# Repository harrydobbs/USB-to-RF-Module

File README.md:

# USB-to-RF-Module
STM32L4-based RF-to-USB dongle using a low-power NRF24 2.4GHz transceiver. <br>
This repository features a custom 3D printed case, firmware and drivers aswell as schematics and PCB layout.

## KiCAD 3D Model

## Assembled Module

## 3D Printed Case

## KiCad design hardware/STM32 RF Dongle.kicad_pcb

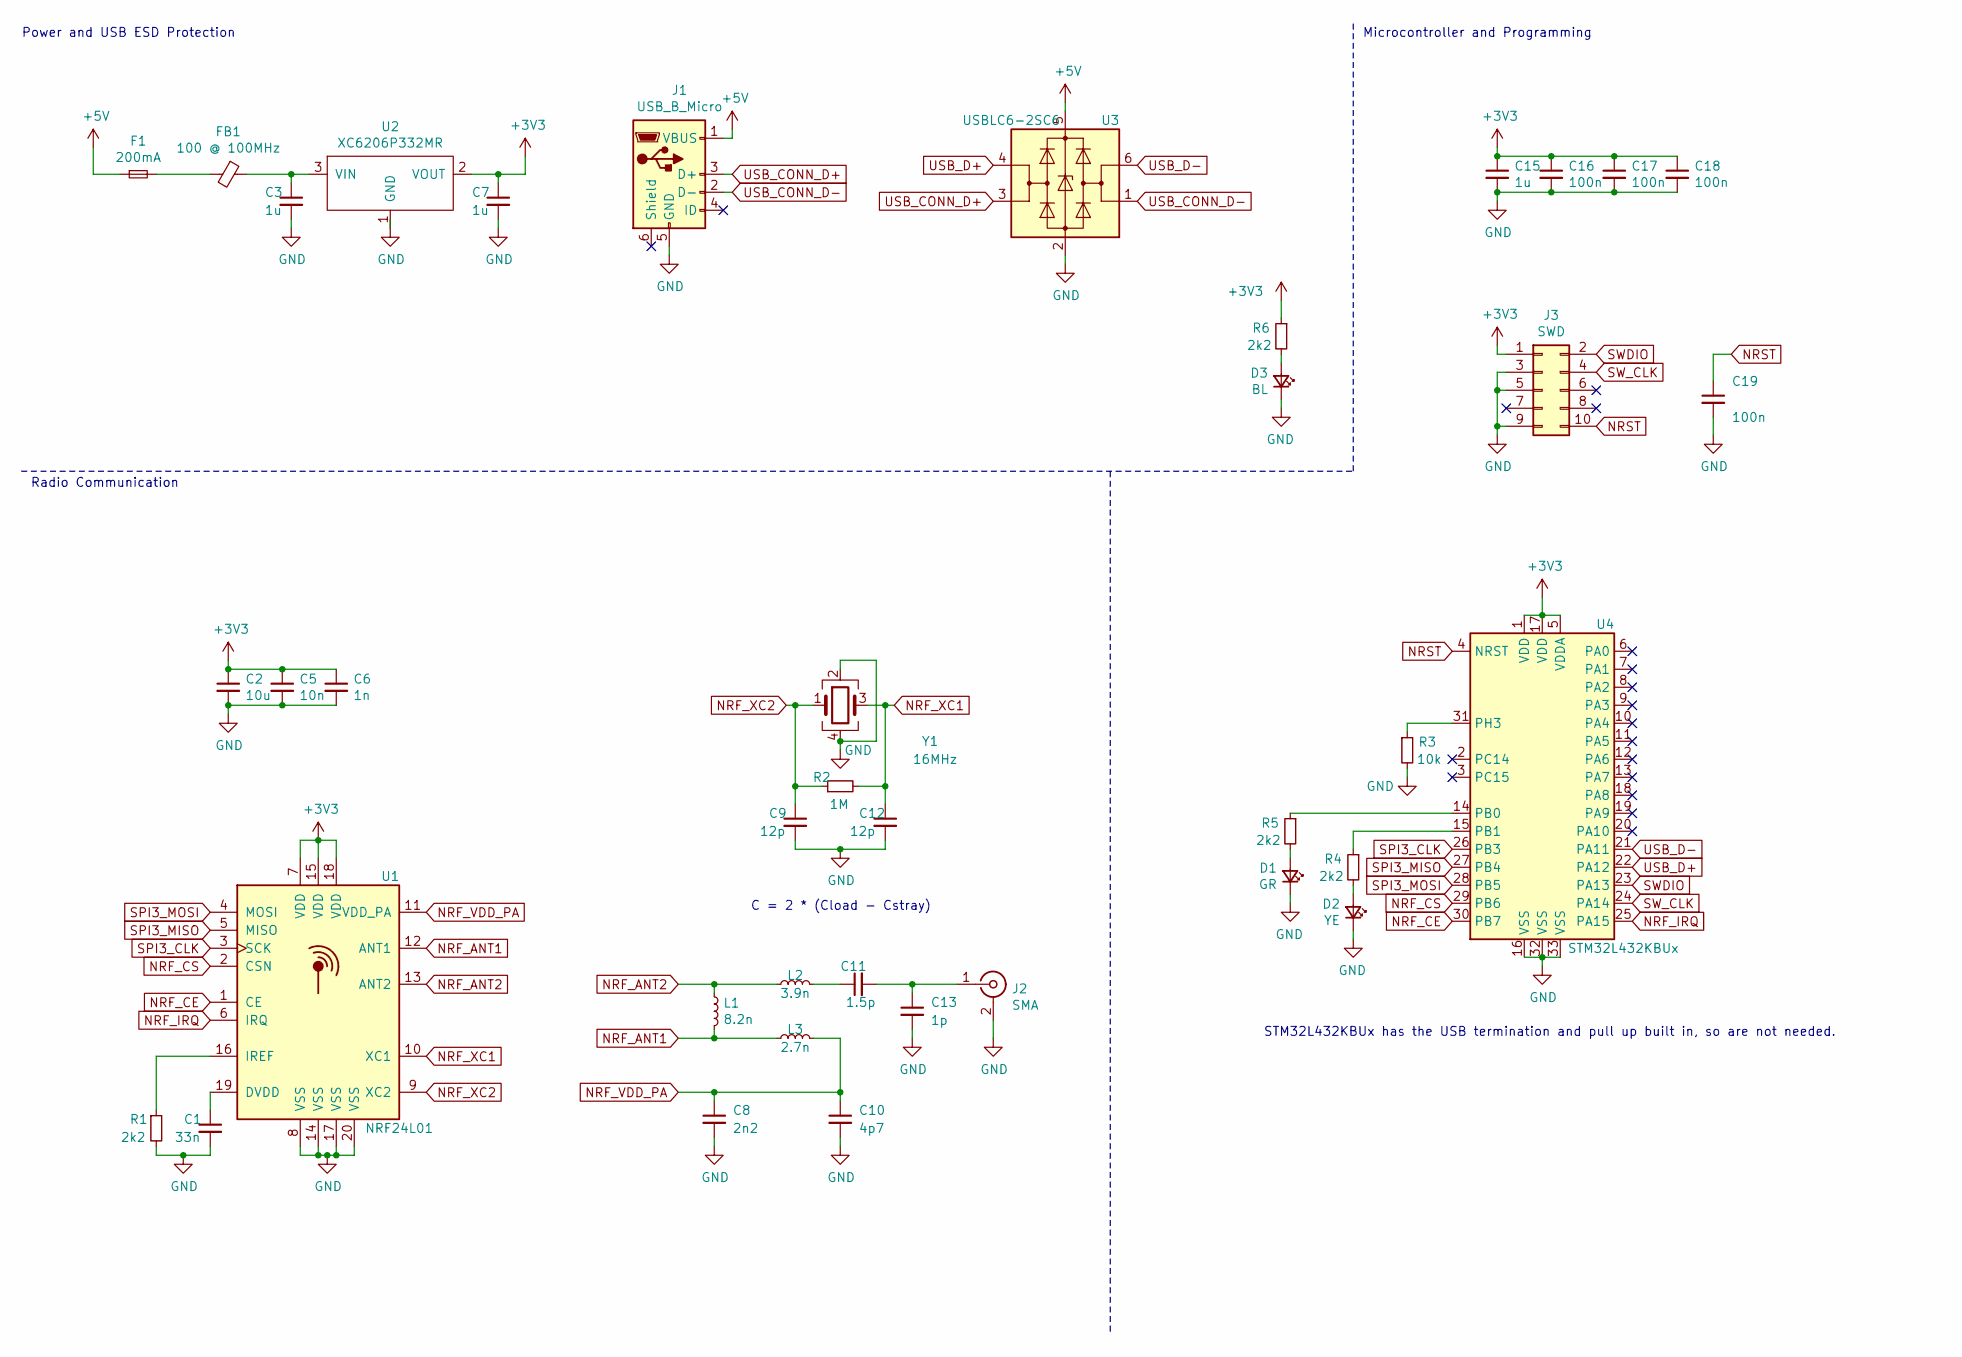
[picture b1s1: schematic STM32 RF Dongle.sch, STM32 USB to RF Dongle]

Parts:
C1: 33n; C_0402_1005Metric; LCSC Part # C1585
C2: 10u; C_0402_1005Metric; LCSC Part # C15525
C3, C7: 1u; C_1206_3216Metric; LCSC Part # C1848
C5: 10n; C_0402_1005Metric; LCSC Part # C15195
C6: 1n; C_0402_1005Metric; LCSC Part # C1523
C8: 2n2; C_0402_1005Metric; LCSC Part # C1531
C9, C12: 12p; C_0402_1005Metric; LCSC Part # C1547
C10: 4p7; C_0402_1005Metric; LCSC Part # C1569
C11: 1.5p; C_0402_1005Metric; LCSC Part # C1552
C13: 1p; C_0402_1005Metric; LCSC Part # C1550
C15: 1u; C_0402_1005Metric; LCSC Part # C52923
C16, C17, C18, C19: 100n; C_0402_1005Metric; LCSC Part # C1525
D1: GR; LED_0603_1608Metric; LCSC Part # C72043
D2: YE; LED_0603_1608Metric; LCSC Part # C72038
D3: BL; LED_0603_1608Metric; LCSC Part # C2286
F1: 200mA; Fuse_1206_3216Metric; LCSC Part # C315892
FB1: 100 @ 100MHz; Fuse_1206_3216Metric; LCSC Part # C124093
J1: USB_B_Micro; USB_Micro-B_Molex-105017-0001
J2: SMA; SMA_Samtec_SMA-J-P-X-ST-EM1_EdgeMount
J3: SWD; PinHeader_2x05_P1.27mm_Vertical
L1: 8.2n; L_0402_1005Metric; LCSC Part # C16208
L2: 3.9n; L_0402_1005Metric; LCSC Part # C14033
L3: 2.7n; L_0402_1005Metric; LCSC Part # C27123
R1: 2k2; R_0402_1005Metric; LCSC Part # C4190
R2: 1M; R_0402_1005Metric; LCSC Part # C22935
R3: 10k; R_0402_1005Metric; LCSC Part # C25804
R4, R5, R6: 2k2; R_0603_1608Metric; LCSC Part # C4190
U1: NRF24L01; QFN-20-1EP_4x4mm_P0.5mm_EP2.5x2.5mm; LCSC Part # C8791
U2: XC6206P332MR; SOT-23; LCSC Part # C5446
U3: USBLC6-2SC6; SOT-23-6
U4: STM32L432KBUx; QFN-32-1EP_5x5mm_P0.5mm_EP3.45x3.45mm; LCSC Part # C94784
Y1: 16MHz; Crystal_SMD_3225-4Pin_3.2x2.5mm; LCSC Part # C13738

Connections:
+3V3: C2.1, C5.1, C6.1, C7.1, C15.1, C16.1, C17.1, C18.1, J3.1, R6.1, U1.7 (VDD), U1.15 (VDD), U1.18 (VDD), U2.2 (VOUT), U4.1 (VDD), U4.5 (VDDA), U4.17 (VDD)
+5V: F1.1, J1.1 (VBUS), U3.5 (VBUS)
GND: C1.2, C2.2, C3.2, C5.2, C6.2, C7.2, C8.2, C9.2, C10.2, C12.2, C13.2, C15.2, C16.2, C17.2, C18.2, C19.2, D1.1 (K), D2.1 (K), D3.1 (K), J1.5 (GND), J2.2 (Ext), J3.3, J3.5, J3.9, R1.2, R3.2, U1.8 (VSS), U1.14 (VSS), U1.17 (VSS), U1.20 (VSS), U2.1 (GND), U3.2 (GND), U4.16 (VSS), U4.32 (VSS), U4.33 (VSS), Y1.2, Y1.4
NRF_ANT1: L1.2, L3.1, U1.12 (ANT1)
NRF_ANT2: L1.1, L2.1, U1.13 (ANT2)
NRF_CE: U1.1 (CE), U4.30 (PB7)
NRF_CS: U1.2 (CSN), U4.29 (PB6)
NRF_IRQ: U1.6 (IRQ), U4.25 (PA15)
NRF_VDD_PA: C8.1, C10.1, L3.2, U1.11 (VDD_PA)
NRF_XC1: C12.1, R2.2, U1.10 (XC1), Y1.3
NRF_XC2: C9.1, R2.1, U1.9 (XC2), Y1.1
NRST: C19.1, J3.10, U4.4 (NRST)
unnamed: C1.1, U1.19 (DVDD)
unnamed: C3.1, FB1.1, U2.3 (VIN)
unnamed: C11.1, L2.2
unnamed: C11.2, C13.1, J2.1 (In)
unnamed: D1.2 (A), R5.2
unnamed: D2.2 (A), R4.2
unnamed: D3.2 (A), R6.2
unnamed: F1.2, FB1.2
unnamed: R1.1, U1.16 (IREF)
unnamed: R3.1, U4.31 (PH3)
unnamed: R4.1, U4.15 (PB1)
unnamed: R5.1, U4.14 (PB0)
SPI3_CLK: U1.3 (SCK), U4.26 (PB3)
SPI3_MISO: U1.5 (MISO), U4.27 (PB4)
SPI3_MOSI: U1.4 (MOSI), U4.28 (PB5)
SWDIO: J3.2, U4.23 (PA13)
SW_CLK: J3.4, U4.24 (PA14)
USB_CONN_D+: J1.3 (D+), U3.3 (I/O2)
USB_CONN_D-: J1.2 (D-), U3.1 (I/O1)
USB_D+: U3.4 (I/O2), U4.22 (PA12)
USB_D-: U3.6 (I/O1), U4.21 (PA11)

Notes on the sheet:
C = 2 * (Cload - Cstray)
STM32L432KBUx has the USB termination and pull up built in, so are not needed.
Radio Communication
Power and USB ESD Protection
Microcontroller and Programming

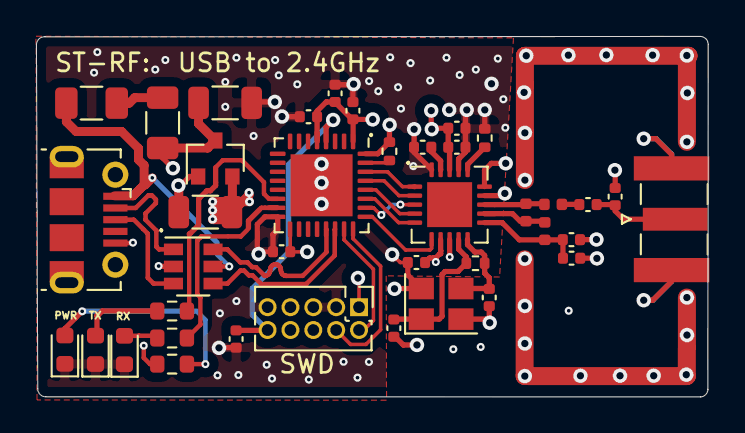
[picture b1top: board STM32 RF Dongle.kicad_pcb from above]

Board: 4 copper layers, 37.3 x 20.0 mm, 39 parts (0 on the bottom side), 33 nets.

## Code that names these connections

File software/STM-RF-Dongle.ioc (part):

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PA14\ (JTCK-SWCLK).Mode=Serial_Wire
PA15\ (JTDI).GPIOParameters=GPIO_Label
Mcu.UserName=STM32L432KBUx
PA11.Mode=Device
PB6.GPIO_Label=NRF CS
PB0.GPIO_Label=RX_LED
PA15\ (JTDI).Signal=GPIO_Input
RCC.SYSCLKSource=RCC_SYSCLKSOURCE_PLLCLK
PB3\ (JTDO-TRACESWO).Signal=SPI3_SCK
PA14\ (JTCK-SWCLK).Signal=SYS_JTCK-SWCLK
PA12.Signal=USB_DP
PB7.GPIOParameters=GPIO_Label
PB6.Signal=GPIO_Output
RCC.HSE_VALUE=8000000
board=custom
PB0.GPIOParameters=GPIO_Label
PB3\ (JTDO-TRACESWO).Mode=Full_Duplex_Master
PB1.GPIO_Label=TX_LED
PB5.Mode=Full_Duplex_Master
PB7.Signal=GPIO_Output
PB4\ (NJTRST).Mode=Full_Duplex_Master
PA15\ (JTDI).GPIO_Label=NRF IRQ
Mcu.Name=STM32L432K(B-C)Ux
PB6.GPIOParameters=GPIO_Label
PB7.GPIO_Label=NRF CE
PA13\ (JTMS-SWDIO).Mode=Serial_Wire
RCC.SYSCLKFreq_VALUE=80000000
Mcu.Package=UFQFPN32
PB5.Signal=SPI3_MOSI
PB1.Signal=GPIO_Output
PA12.Mode=Device
PA11.Signal=USB_DM
PA13\ (JTMS-SWDIO).Signal=SYS_JTMS-SWDIO
PB0.Signal=GPIO_Output
PB1.GPIOParameters=GPIO_Label
PB4\ (NJTRST).Signal=SPI3_MISO

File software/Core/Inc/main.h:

/* USER CODE BEGIN Header */
/**
  ******************************************************************************
  * @file           : main.h
  * @brief          : Header for main.c file.
  *                   This file contains the common defines of the application.
  ******************************************************************************
  * @attention
  *
  * <h2><center>&copy; Copyright (c) 2021 STMicroelectronics.
  * All rights reserved.</center></h2>
  *
  * This software component is licensed by ST under BSD 3-Clause license,
  * the "License"; You may not use this file except in compliance with the
  * License. You may obtain a copy of the License at:
  *                        opensource.org/licenses/BSD-3-Clause
  *
  ******************************************************************************
  */
/* USER CODE END Header */

/* Define to prevent recursive inclusion -------------------------------------*/
#ifndef __MAIN_H
#define __MAIN_H

#ifdef __cplusplus
extern "C" {
#endif

/* Includes ------------------------------------------------------------------*/
#include "stm32l4xx_hal.h"

/* Private includes ----------------------------------------------------------*/
/* USER CODE BEGIN Includes */
#define MODE 1 // RX (1) or TX (0)1
SPI_HandleTypeDef hspi3;
/* USER CODE END Includes */

/* Exported types ------------------------------------------------------------*/
/* USER CODE BEGIN ET */

/* USER CODE END ET */

/* Exported constants --------------------------------------------------------*/
/* USER CODE BEGIN EC */

/* USER CODE END EC */

/* Exported macro ------------------------------------------------------------*/
/* USER CODE BEGIN EM */

/* USER CODE END EM */

/* Exported functions prototypes ---------------------------------------------*/
void Error_Handler(void);

/* USER CODE BEGIN EFP */

/* USER CODE END EFP */

/* Private defines -----------------------------------------------------------*/
#define RX_LED_Pin GPIO_PIN_0
#define RX_LED_GPIO_Port GPIOB
#define TX_LED_Pin GPIO_PIN_1
#define TX_LED_GPIO_Port GPIOB
#define NRF_IRQ_Pin GPIO_PIN_15
#define NRF_IRQ_GPIO_Port GPIOA
#define NRF_CS_Pin GPIO_PIN_6
#define NRF_CS_GPIO_Port GPIOB
#define NRF_CE_Pin GPIO_PIN_7
#define NRF_CE_GPIO_Port GPIOB
/* USER CODE BEGIN Private defines */

/* USER CODE END Private defines */

#ifdef __cplusplus
}
#endif

#endif /* __MAIN_H */

/************************ (C) COPYRIGHT STMicroelectronics *****END OF FILE****/

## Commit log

2021-01-20 added image and minor schematic tidy up
2021-01-20 images
2021-04-26 added 3d pritnable case
2021-04-26 added 3d pritnable case photo
2021-05-06 rx kinda working but only with one byte
2021-05-07 fixed usb recieve issue
2021-05-07 about to change bit size
2021-05-07 pre ioc reconfig
2021-05-07 LED be flashing
2021-05-07 done for the night almost got RX working...:
2021-05-08 unsure why tis not working , registers look okay , obviously RX fifo is not filling up tho?
2021-05-08 It is working now range seems poor and drops out?
2021-05-10 sorta working , huge packet loss and packet errors
